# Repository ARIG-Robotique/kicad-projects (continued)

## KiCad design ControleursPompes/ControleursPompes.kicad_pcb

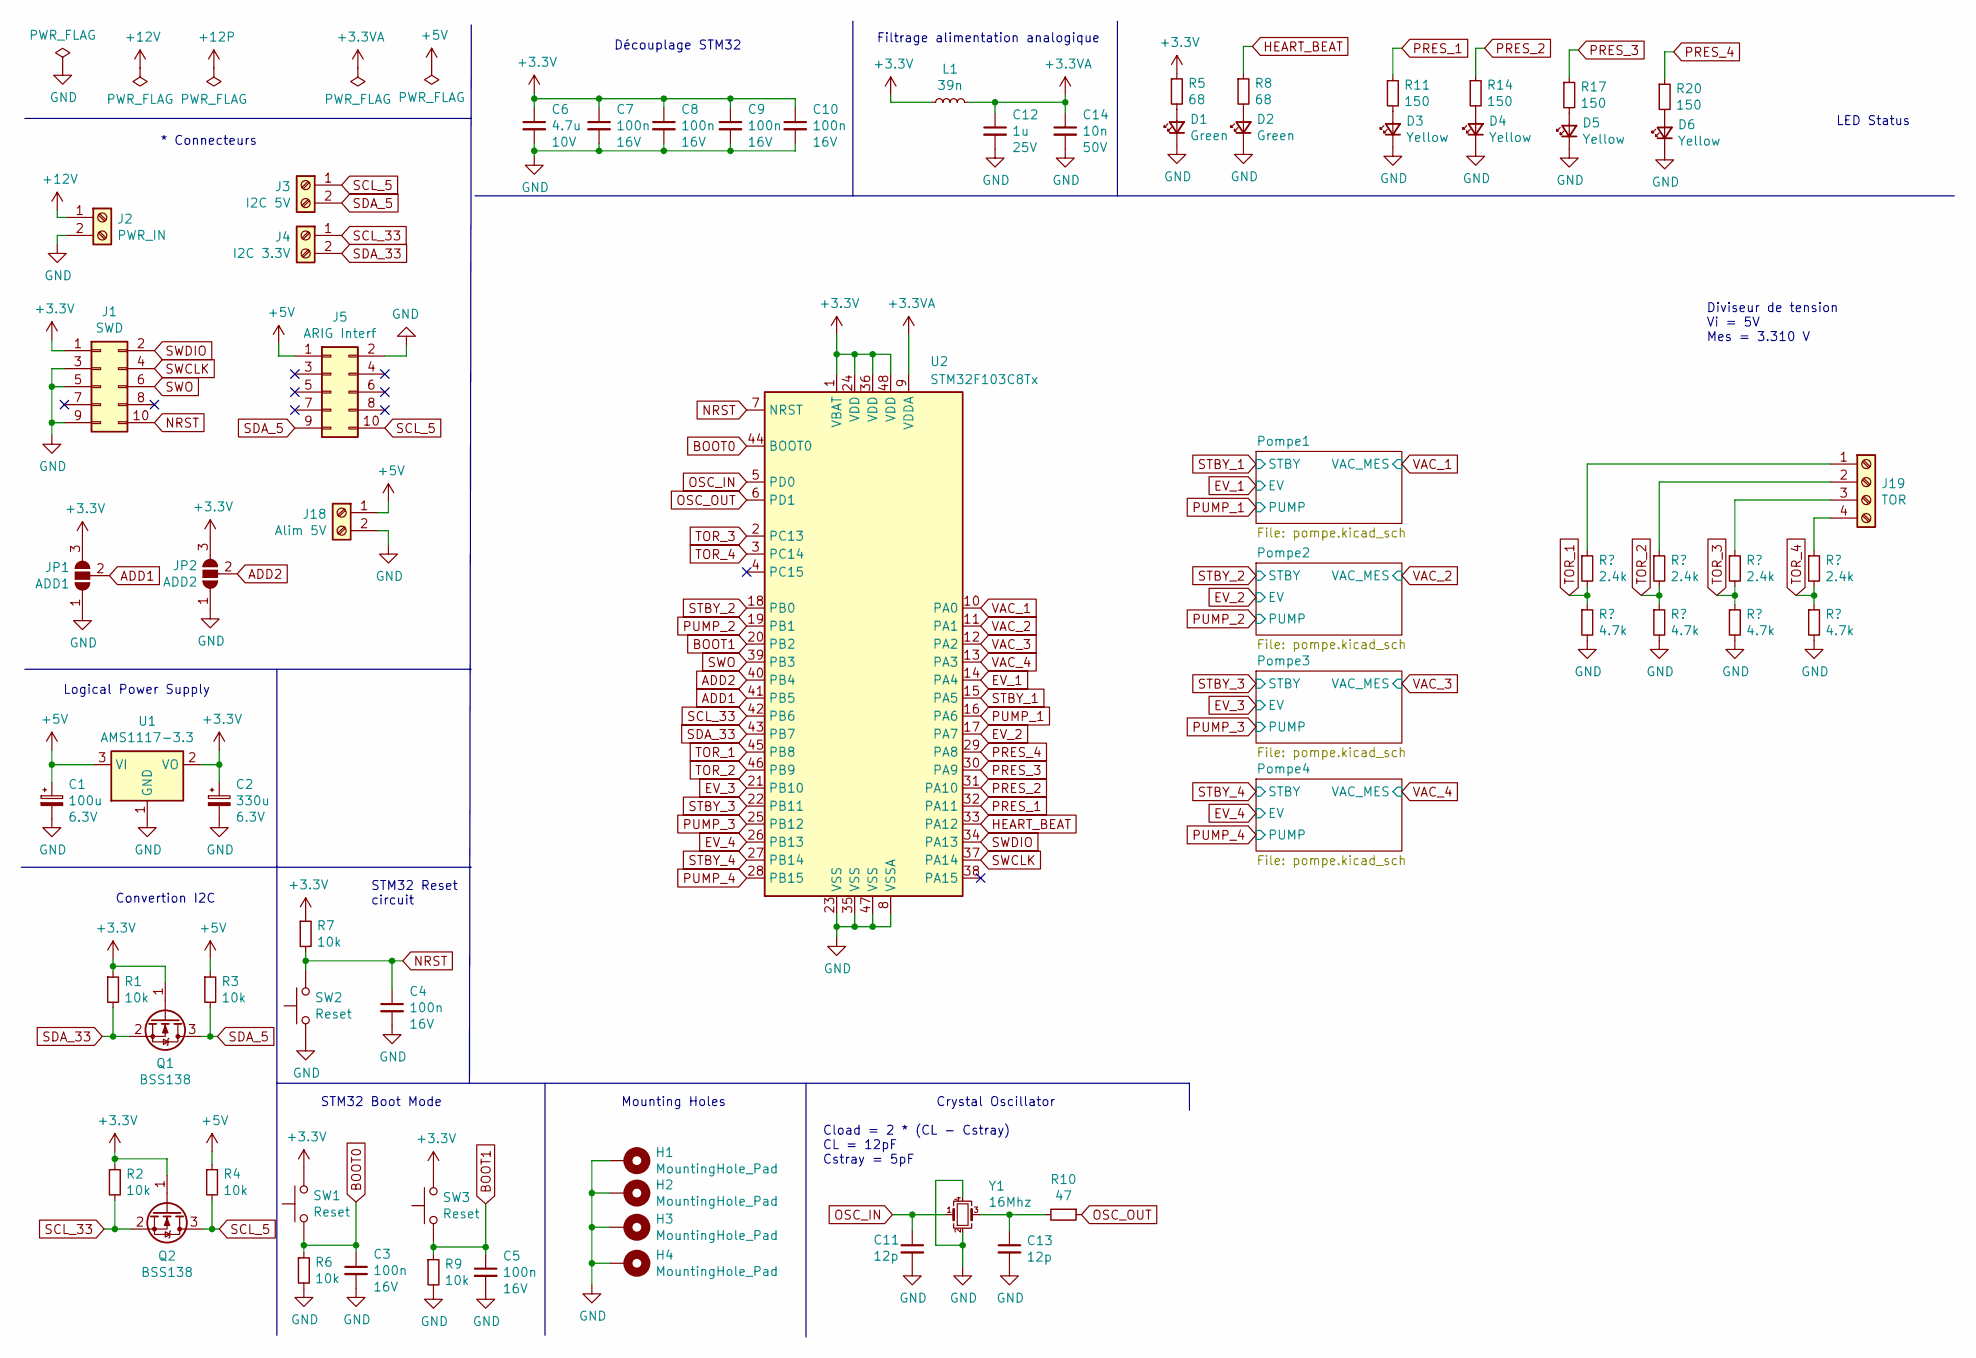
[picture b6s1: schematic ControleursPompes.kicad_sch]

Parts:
C1: 100u; CP_Elec_5x5.3; LCSC Part C249463
C2: 330u; CP_Elec_6.3x7.7; LCSC Part C249900
C3, C4, C5, C7, C8, C9, C10: 100n; C_0402_1005Metric_Pad0.74x0.62mm_HandSolder; LCSC Part C1525
C6: 4.7u; C_0402_1005Metric_Pad0.74x0.62mm_HandSolder; LCSC Part C23733
C11, C13: 12p; C_0402_1005Metric_Pad0.74x0.62mm_HandSolder; LCSC Part C1547
C12: 1u; C_0402_1005Metric_Pad0.74x0.62mm_HandSolder; LCSC Part C52923
C14: 10n; C_0402_1005Metric_Pad0.74x0.62mm_HandSolder; LCSC Part C15195
D1, D2: Green; LED_0805_2012Metric_Pad1.15x1.40mm_HandSolder; LCSC Part C63855
D3, D4, D5, D6: Yellow; LED_0805_2012Metric_Pad1.15x1.40mm_HandSolder; LCSC Part C74346
H1, H2, H3, H4: MountingHole_Pad; MountingHole_3.2mm_M3_Pad_Via; JLCPCB BOM 0
J1: SWD; PinHeader_2x05_P1.27mm_Vertical; JLCPCB BOM 0
J2: PWR_IN; TerminalBlock_Phoenix_MKDS-1,5-2-5.08_1x02_P5.08mm_Horizont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; JLCPCB BOM 0
J3: I2C 5V; TerminalBlock_Phoenix_MPT-0,5-2-2.54_1x02_P2.54mm_Horizontal; JLCPCB BOM 0
J4: I2C 3.3V; TerminalBlock_Phoenix_MPT-0,5-2-2.54_1x02_P2.54mm_Horizontal; JLCPCB BOM 0
J5: ARIG Interf; IDC-Header_2x05_P2.54mm_Vertical; JLCPCB BOM 0
J18: Alim 5V; TerminalBlock_Phoenix_MPT-0,5-2-2.54_1x02_P2.54mm_Horizontal; JLCPCB BOM 0
J19: TOR; TerminalBlock_Phoenix_MPT-0,5-4-2.54_1x04_P2.54mm_Horizontal; JLCPCB BOM 0
JP1: ADD1; SolderJumper-3_P1.3mm_Open_RoundedPad1.0x1.5mm; JLCPCB BOM 0
JP2: ADD2; SolderJumper-3_P1.3mm_Open_RoundedPad1.0x1.5mm; JLCPCB BOM 0
L1: 39n; L_0402_1005Metric_Pad0.77x0.64mm_HandSolder; LCSC Part C26443
Q1, Q2: BSS138; SOT-23; LCSC Part C426569
R1, R2, R3, R4, R6, R7, R9: 10k; R_0805_2012Metric_Pad1.20x1.40mm_HandSolder; LCSC Part C17414
R5, R8: 68; R_0805_2012Metric_Pad1.20x1.40mm_HandSolder; LCSC Part C17802
R10: 47; R_0402_1005Metric_Pad0.72x0.64mm_HandSolder; LCSC Part C25118
R11, R14, R17, R20: 150; R_0805_2012Metric_Pad1.20x1.40mm_HandSolder; LCSC Part C17471
R23, R25, R27, R29: 2.4k; R_0805_2012Metric_Pad1.20x1.40mm_HandSolder; LCSC Part C17526
R24, R26, R28, R30: 4.7k; R_0805_2012Metric_Pad1.20x1.40mm_HandSolder; LCSC Part C17673
SW1, SW2, SW3: Reset; SW_TS_1088_AR_3x4x2; LCSC Part C720477
U1: AMS1117-3.3; SOT-223-3_TabPin2; LCSC Part C6186
U2: STM32F103C8Tx; LQFP-48_7x7mm_P0.5mm; LCSC Part C8734
Y1: 16Mhz; Crystal_SMD_3225-4Pin_3.2x2.5mm_HandSoldering; LCSC Part C13738

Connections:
+3.3VA: C12.1, C14.1, L1.2, U2.9 (VDDA)
+3V3: C2.1, C6.1, C7.1, C8.1, C9.1, C10.1, J1.1, JP1.3 (B), JP2.3 (B), L1.1, Q1.1 (G), Q2.1 (G), R1.1, R2.1, R5.1, R7.1, SW1.1, SW3.1, U1.2 (VO), U2.1 (VBAT), U2.24 (VDD), U2.36 (VDD), U2.48 (VDD); also elsewhere on the board
+5V: C1.1, J5.1, J18.1, R3.1, R4.1, U1.3 (VI)
+12V: J2.1; also elsewhere on the board
ADD1: JP1.2 (C), U2.41 (PB5)
ADD2: JP2.2 (C), U2.40 (PB4)
BOOT0: C3.1, R6.1, SW1.2, U2.44 (BOOT0)
BOOT1: C5.1, R9.1, SW3.2, U2.20 (PB2)
EV_1: U2.14 (PA4); also elsewhere on the board
EV_2: U2.17 (PA7); also elsewhere on the board
EV_3: U2.21 (PB10); also elsewhere on the board
EV_4: U2.26 (PB13); also elsewhere on the board
GND: C1.2, C2.2, C3.2, C4.2, C5.2, C6.2, C7.2, C8.2, C9.2, C10.2, C11.2, C12.2, C13.2, C14.2, D1.1 (K), D2.1 (K), D3.1 (K), D4.1 (K), D5.1 (K), D6.1 (K), H1.1, H2.1, H3.1, H4.1, J1.3, J1.5, J1.9, J2.2, J5.2, J18.2, JP1.1 (A), JP2.1 (A), R6.2, R9.2, R24.2, R26.2, R28.2, R30.2, SW2.2, U1.1 (GND), U2.8 (VSSA), U2.23 (VSS), U2.35 (VSS), U2.47 (VSS), Y1.2, Y1.4; also elsewhere on the board
HEART_BEAT: R8.1, U2.33 (PA12)
NRST: C4.1, J1.10, R7.2, SW2.1, U2.7 (NRST)
unnamed: C13.1, R10.2, Y1.3
unnamed: D1.2 (A), R5.2
unnamed: D2.2 (A), R8.2
unnamed: D3.2 (A), R11.2
unnamed: D4.2 (A), R14.2
unnamed: D5.2 (A), R17.2
unnamed: D6.2 (A), R20.2
unnamed: J19.1, R23.1
unnamed: J19.2, R25.1
unnamed: J19.3, R27.1
unnamed: J19.4, R29.1
OSC_IN: C11.1, U2.5 (PD0), Y1.1
OSC_OUT: R10.1, U2.6 (PD1)
PRES_1: R11.1, U2.32 (PA11)
PRES_2: R14.1, U2.31 (PA10)
PRES_3: R17.1, U2.30 (PA9)
PRES_4: R20.1, U2.29 (PA8)
PUMP_1: U2.16 (PA6); also elsewhere on the board
PUMP_2: U2.19 (PB1); also elsewhere on the board
PUMP_3: U2.25 (PB12); also elsewhere on the board
PUMP_4: U2.28 (PB15); also elsewhere on the board
SCL_5: J3.1, J5.10, Q2.3 (D), R4.2
SCL_33: J4.1, Q2.2 (S), R2.2, U2.42 (PB6)
SDA_5: J3.2, J5.9, Q1.3 (D), R3.2
SDA_33: J4.2, Q1.2 (S), R1.2, U2.43 (PB7)
STBY_1: U2.15 (PA5); also elsewhere on the board
STBY_2: U2.18 (PB0); also elsewhere on the board
STBY_3: U2.22 (PB11); also elsewhere on the board
STBY_4: U2.27 (PB14); also elsewhere on the board
SWCLK: J1.4, U2.37 (PA14)
SWDIO: J1.2, U2.34 (PA13)
SWO: J1.6, U2.39 (PB3)
TOR_1: R23.2, R24.1, U2.45 (PB8)
TOR_2: R25.2, R26.1, U2.46 (PB9)
TOR_3: R27.2, R28.1, U2.2 (PC13)
TOR_4: R29.2, R30.1, U2.3 (PC14)
VAC_1: U2.10 (PA0); also elsewhere on the board
VAC_2: U2.11 (PA1); also elsewhere on the board
VAC_3: U2.12 (PA2); also elsewhere on the board
VAC_4: U2.13 (PA3); also elsewhere on the board

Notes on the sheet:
STM32 Reset circuit
Diviseur de tension Vi = 5V Mes = 3.310 V
Convertion I2C
Logical Power Supply
Mounting Holes
LED Status
Cload = 2 * (CL - Cstray) CL = 12pF Cstray = 5pF
STM32 Boot Mode
Filtrage alimentation analogique
* Connecteurs
Découplage STM32
Crystal Oscillator

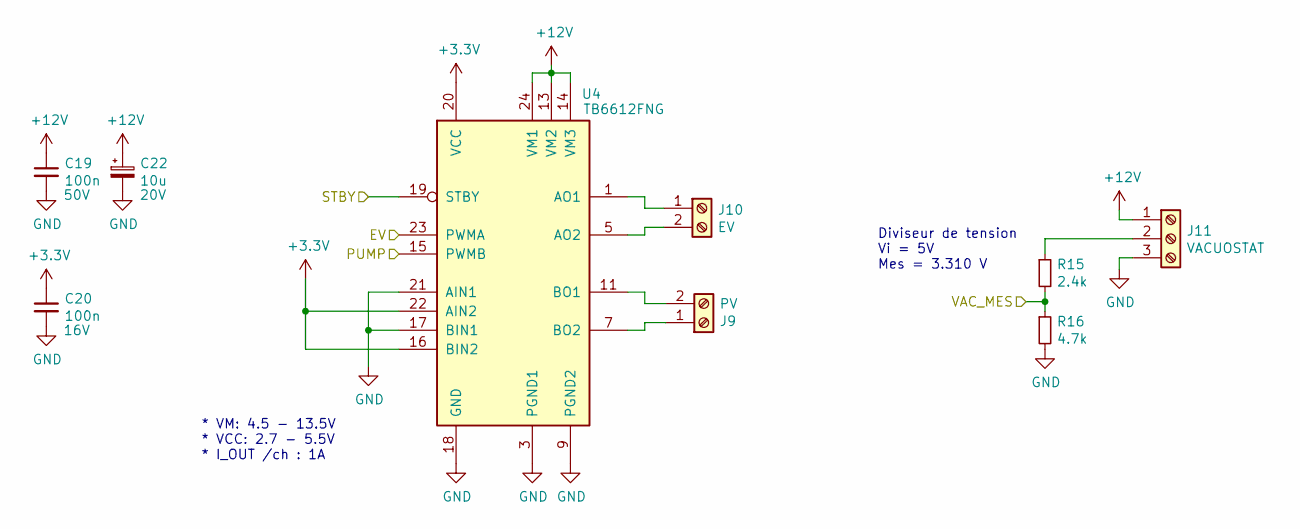
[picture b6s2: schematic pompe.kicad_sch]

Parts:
C19: 100n; C_0805_2012Metric_Pad1.18x1.45mm_HandSolder; LCSC Part C49678
C20: 100n; C_0402_1005Metric_Pad0.74x0.62mm_HandSolder; LCSC Part C1525
C22: 10u; CP_EIA-3528-21_Kemet-B_Pad1.50x2.35mm_HandSolder; LCSC Part C180482
J9: PV; TerminalBlock_Phoenix_MPT-0,5-2-2.54_1x02_P2.54mm_Horizontal; JLCPCB BOM 0
J10: EV; TerminalBlock_Phoenix_MPT-0,5-2-2.54_1x02_P2.54mm_Horizontal; JLCPCB BOM 0
J11: VACUOSTAT; TerminalBlock_Phoenix_MPT-0,5-3-2.54_1x03_P2.54mm_Horizontal; JLCPCB BOM 0
R15: 2.4k; R_0805_2012Metric_Pad1.20x1.40mm_HandSolder; LCSC Part C17526
R16: 4.7k; R_0805_2012Metric_Pad1.20x1.40mm_HandSolder; LCSC Part C17673
U4: TB6612FNG; SSOP-24_5.3x8.2mm_P0.65mm; LCSC Part C88224

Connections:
+3V3: C20.1, U4.16 (BIN2), U4.20 (VCC), U4.22 (AIN2); also elsewhere on the board
+12V: C19.1, C22.1, J11.1, U4.13 (VM2), U4.14 (VM3), U4.24 (VM1); also elsewhere on the board
EV_2: U4.23 (PWMA); also elsewhere on the board
GND: C19.2, C20.2, C22.2, J11.3, R16.2, U4.3 (PGND1), U4.4 (PGND1), U4.9 (PGND2), U4.10 (PGND2), U4.17 (BIN1), U4.18 (GND), U4.21 (AIN1); also elsewhere on the board
unnamed: J9.1, U4.7 (BO2), U4.8 (BO2)
unnamed: J9.2, U4.11 (BO1), U4.12 (BO1)
unnamed: J10.1, U4.1 (AO1), U4.2 (AO1)
unnamed: J10.2, U4.5 (AO2), U4.6 (AO2)
unnamed: J11.2, R15.1
PUMP_2: U4.15 (PWMB); also elsewhere on the board
STBY_2: U4.19 (STBY); also elsewhere on the board
VAC_2: R15.2, R16.1; also elsewhere on the board

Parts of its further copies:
C15, C23, C27: 100n; C_0805_2012Metric_Pad1.18x1.45mm_HandSolder; LCSC Part C49678
C16, C24, C28: 100n; C_0402_1005Metric_Pad0.74x0.62mm_HandSolder; LCSC Part C1525
C18, C26, C30: 10u; CP_EIA-3528-21_Kemet-B_Pad1.50x2.35mm_HandSolder; LCSC Part C180482
J6, J12, J15: PV; TerminalBlock_Phoenix_MPT-0,5-2-2.54_1x02_P2.54mm_Horizontal; JLCPCB BOM 0
J7, J13, J16: EV; TerminalBlock_Phoenix_MPT-0,5-2-2.54_1x02_P2.54mm_Horizontal; JLCPCB BOM 0
J8, J14, J17: VACUOSTAT; TerminalBlock_Phoenix_MPT-0,5-3-2.54_1x03_P2.54mm_Horizontal; JLCPCB BOM 0
R12, R18, R21: 2.4k; R_0805_2012Metric_Pad1.20x1.40mm_HandSolder; LCSC Part C17526
R13, R19, R22: 4.7k; R_0805_2012Metric_Pad1.20x1.40mm_HandSolder; LCSC Part C17673
U3, U5, U6: TB6612FNG; SSOP-24_5.3x8.2mm_P0.65mm; LCSC Part C88224

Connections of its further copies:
+3V3: C16.1, C24.1, C28.1, U3.16 (BIN2), U3.20 (VCC), U3.22 (AIN2), U5.16 (BIN2), U5.20 (VCC), U5.22 (AIN2), U6.16 (BIN2), U6.20 (VCC), U6.22 (AIN2); also elsewhere on the board
+12V: C15.1, C18.1, C23.1, C26.1, C27.1, C30.1, J8.1, J14.1, J17.1, U3.13 (VM2), U3.14 (VM3), U3.24 (VM1), U5.13 (VM2), U5.14 (VM3), U5.24 (VM1), U6.13 (VM2), U6.14 (VM3), U6.24 (VM1); also elsewhere on the board
EV_1: U3.23 (PWMA); also elsewhere on the board
EV_3: U5.23 (PWMA); also elsewhere on the board
EV_4: U6.23 (PWMA); also elsewhere on the board
GND: C15.2, C16.2, C18.2, C23.2, C24.2, C26.2, C27.2, C28.2, C30.2, J8.3, J14.3, J17.3, R13.2, R19.2, R22.2, U3.3 (PGND1), U3.4 (PGND1), U3.9 (PGND2), U3.10 (PGND2), U3.17 (BIN1), U3.18 (GND), U3.21 (AIN1), U5.3 (PGND1), U5.4 (PGND1), U5.9 (PGND2), U5.10 (PGND2), U5.17 (BIN1), U5.18 (GND), U5.21 (AIN1), U6.3 (PGND1), U6.4 (PGND1), U6.9 (PGND2), U6.10 (PGND2), U6.17 (BIN1), U6.18 (GND), U6.21 (AIN1); also elsewhere on the board
unnamed: J6.1, U3.7 (BO2), U3.8 (BO2)
unnamed: J6.2, U3.11 (BO1), U3.12 (BO1)
unnamed: J7.1, U3.1 (AO1), U3.2 (AO1)
unnamed: J7.2, U3.5 (AO2), U3.6 (AO2)
unnamed: J8.2, R12.1
unnamed: J12.1, U5.7 (BO2), U5.8 (BO2)
unnamed: J12.2, U5.11 (BO1), U5.12 (BO1)
unnamed: J13.1, U5.1 (AO1), U5.2 (AO1)
unnamed: J13.2, U5.5 (AO2), U5.6 (AO2)
unnamed: J14.2, R18.1
unnamed: J15.1, U6.7 (BO2), U6.8 (BO2)
unnamed: J15.2, U6.11 (BO1), U6.12 (BO1)
unnamed: J16.1, U6.1 (AO1), U6.2 (AO1)
unnamed: J16.2, U6.5 (AO2), U6.6 (AO2)
unnamed: J17.2, R21.1
PUMP_1: U3.15 (PWMB); also elsewhere on the board
PUMP_3: U5.15 (PWMB); also elsewhere on the board
PUMP_4: U6.15 (PWMB); also elsewhere on the board
STBY_1: U3.19 (STBY); also elsewhere on the board
STBY_3: U5.19 (STBY); also elsewhere on the board
STBY_4: U6.19 (STBY); also elsewhere on the board
VAC_1: R12.2, R13.1; also elsewhere on the board
VAC_3: R18.2, R19.1; also elsewhere on the board
VAC_4: R21.2, R22.1; also elsewhere on the board

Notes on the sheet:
* VM: 4.5 - 13.5V * VCC: 2.7 - 5.5V * I_OUT /ch : 1A
Diviseur de tension Vi = 5V Mes = 3.310 V

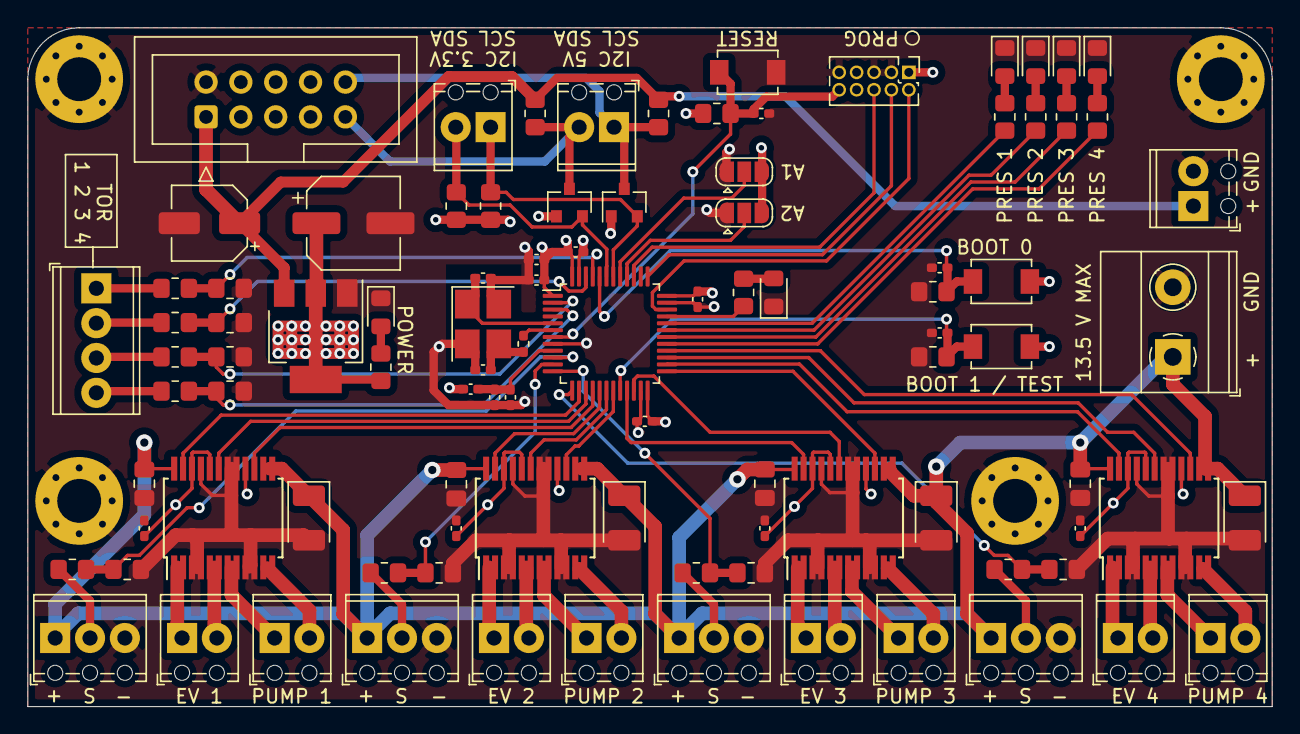
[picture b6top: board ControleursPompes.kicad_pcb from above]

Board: 4 copper layers, 90.8 x 49.5 mm, 100 parts (0 on the bottom side), 75 nets.

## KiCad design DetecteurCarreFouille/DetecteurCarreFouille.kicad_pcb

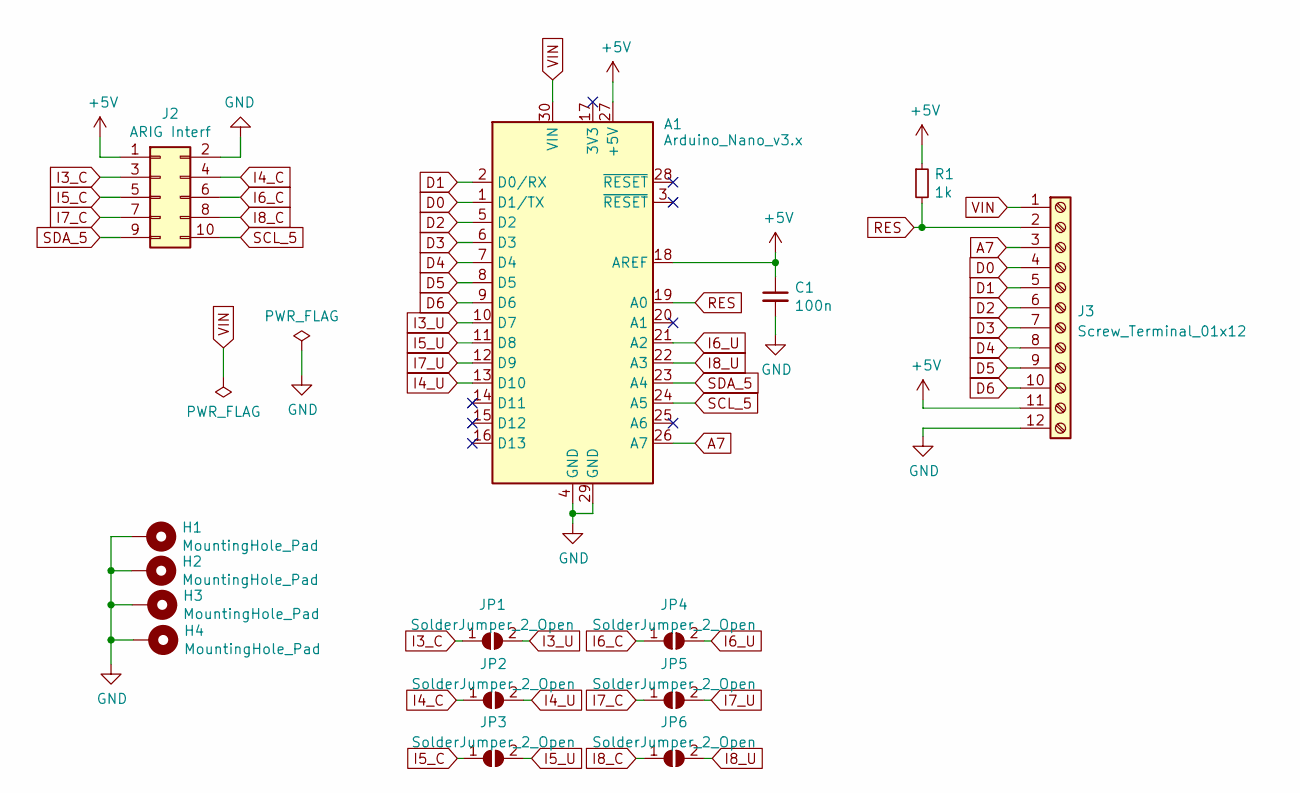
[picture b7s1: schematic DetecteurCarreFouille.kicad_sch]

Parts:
A1: Arduino_Nano_v3.x; Arduino_Nano
C1: 100n; C_Rect_L7.0mm_W2.5mm_P5.00mm
H1, H2, H3, H4: MountingHole_Pad; MountingHole_3.2mm_M3_Pad_Via
J2: ARIG Interf; IDC-Header_2x05_P2.54mm_Vertical
J3: Screw_Terminal_01x12; TerminalBlock_Phoenix_MPT-0,5-12-2.54_1x12_P2.54mm_Horizont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
JP1, JP2, JP3, JP4, JP5, JP6: SolderJumper_2_Open; SolderJumper-2_P1.3mm_Open_RoundedPad1.0x1.5mm
R1: 1k; R_Axial_DIN0309_L9.0mm_D3.2mm_P15.24mm_Horizontal

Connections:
+5V: A1.18 (AREF), A1.27 (+5V), C1.1, J2.1, J3.11, R1.1
A7: A1.26 (A7), J3.3
D0: A1.1 (D1/TX), J3.4
D1: A1.2 (D0/RX), J3.5
D2: A1.5 (D2), J3.6
D3: A1.6 (D3), J3.7
D4: A1.7 (D4), J3.8
D5: A1.8 (D5), J3.9
D6: A1.9 (D6), J3.10
GND: A1.4 (GND), A1.29 (GND), C1.2, H1.1, H2.1, H3.1, H4.1, J2.2, J3.12
I3_C: J2.3, JP1.1 (A)
I3_U: A1.10 (D7), JP1.2 (B)
I4_C: J2.4, JP2.1 (A)
I4_U: A1.13 (D10), JP2.2 (B)
I5_C: J2.5, JP3.1 (A)
I5_U: A1.11 (D8), JP3.2 (B)
I6_C: J2.6, JP4.1 (A)
I6_U: A1.21 (A2), JP4.2 (B)
I7_C: J2.7, JP5.1 (A)
I7_U: A1.12 (D9), JP5.2 (B)
I8_C: J2.8, JP6.1 (A)
I8_U: A1.22 (A3), JP6.2 (B)
RES: A1.19 (A0), J3.2, R1.2
SCL_5: A1.24 (A5), J2.10
SDA_5: A1.23 (A4), J2.9
VIN: A1.30 (VIN), J3.1

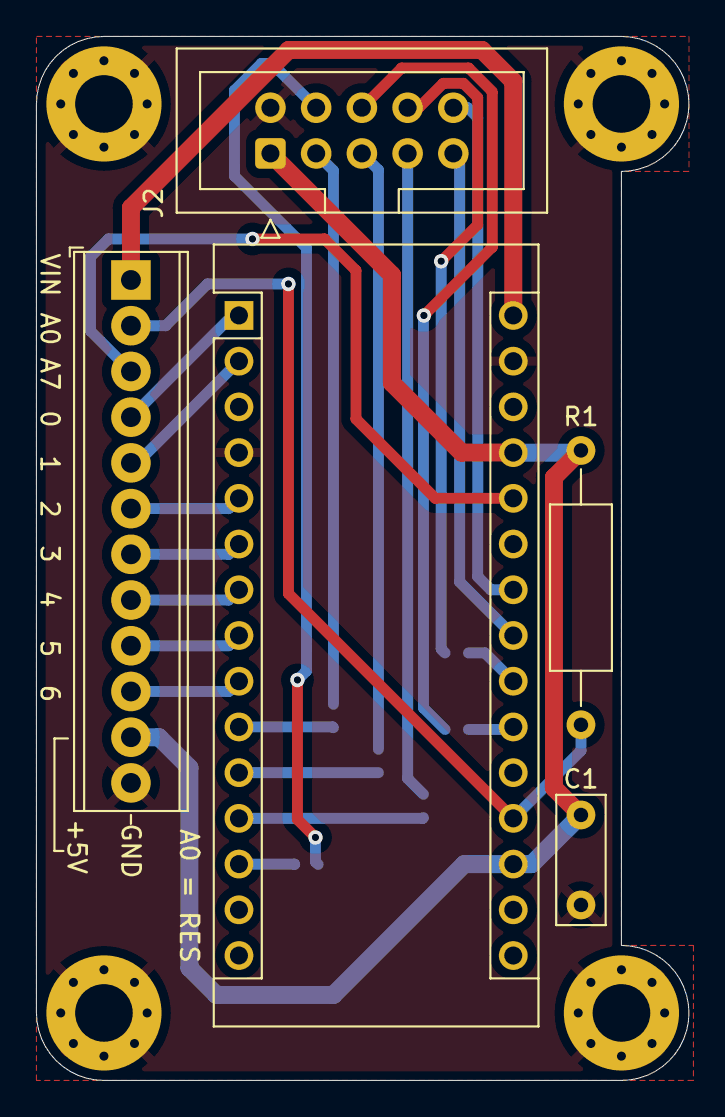
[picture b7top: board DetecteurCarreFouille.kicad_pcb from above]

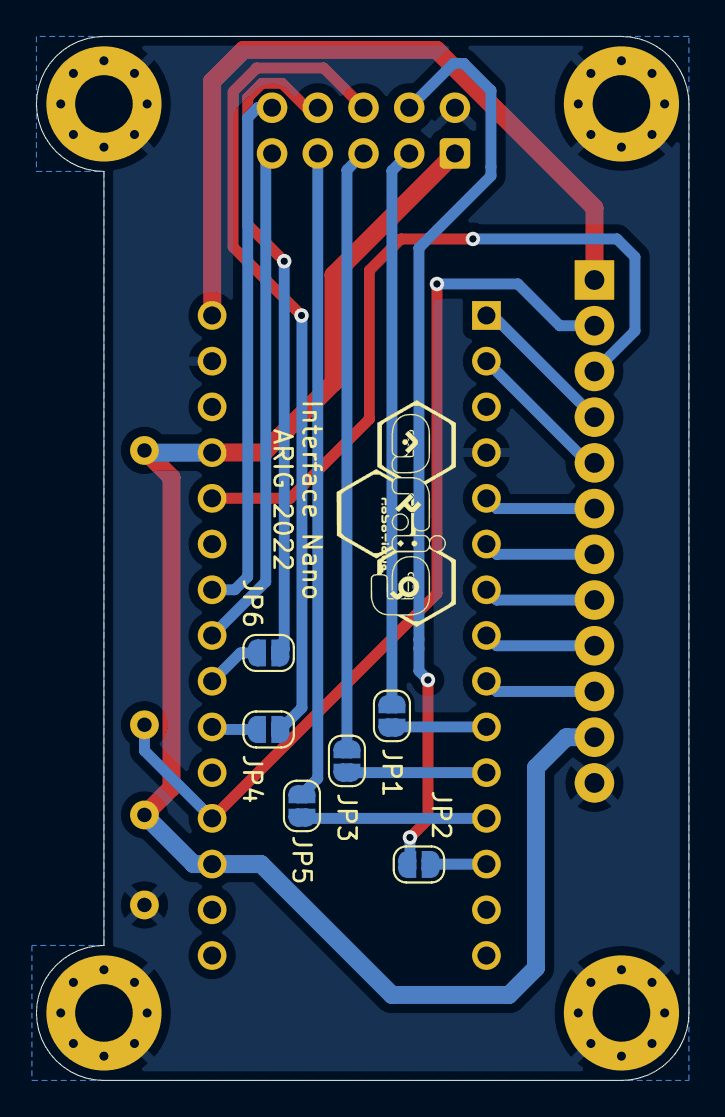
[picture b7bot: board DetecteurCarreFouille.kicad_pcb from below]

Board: 2 copper layers, 36.2 x 58.0 mm, 15 parts (6 on the bottom side), 26 nets.

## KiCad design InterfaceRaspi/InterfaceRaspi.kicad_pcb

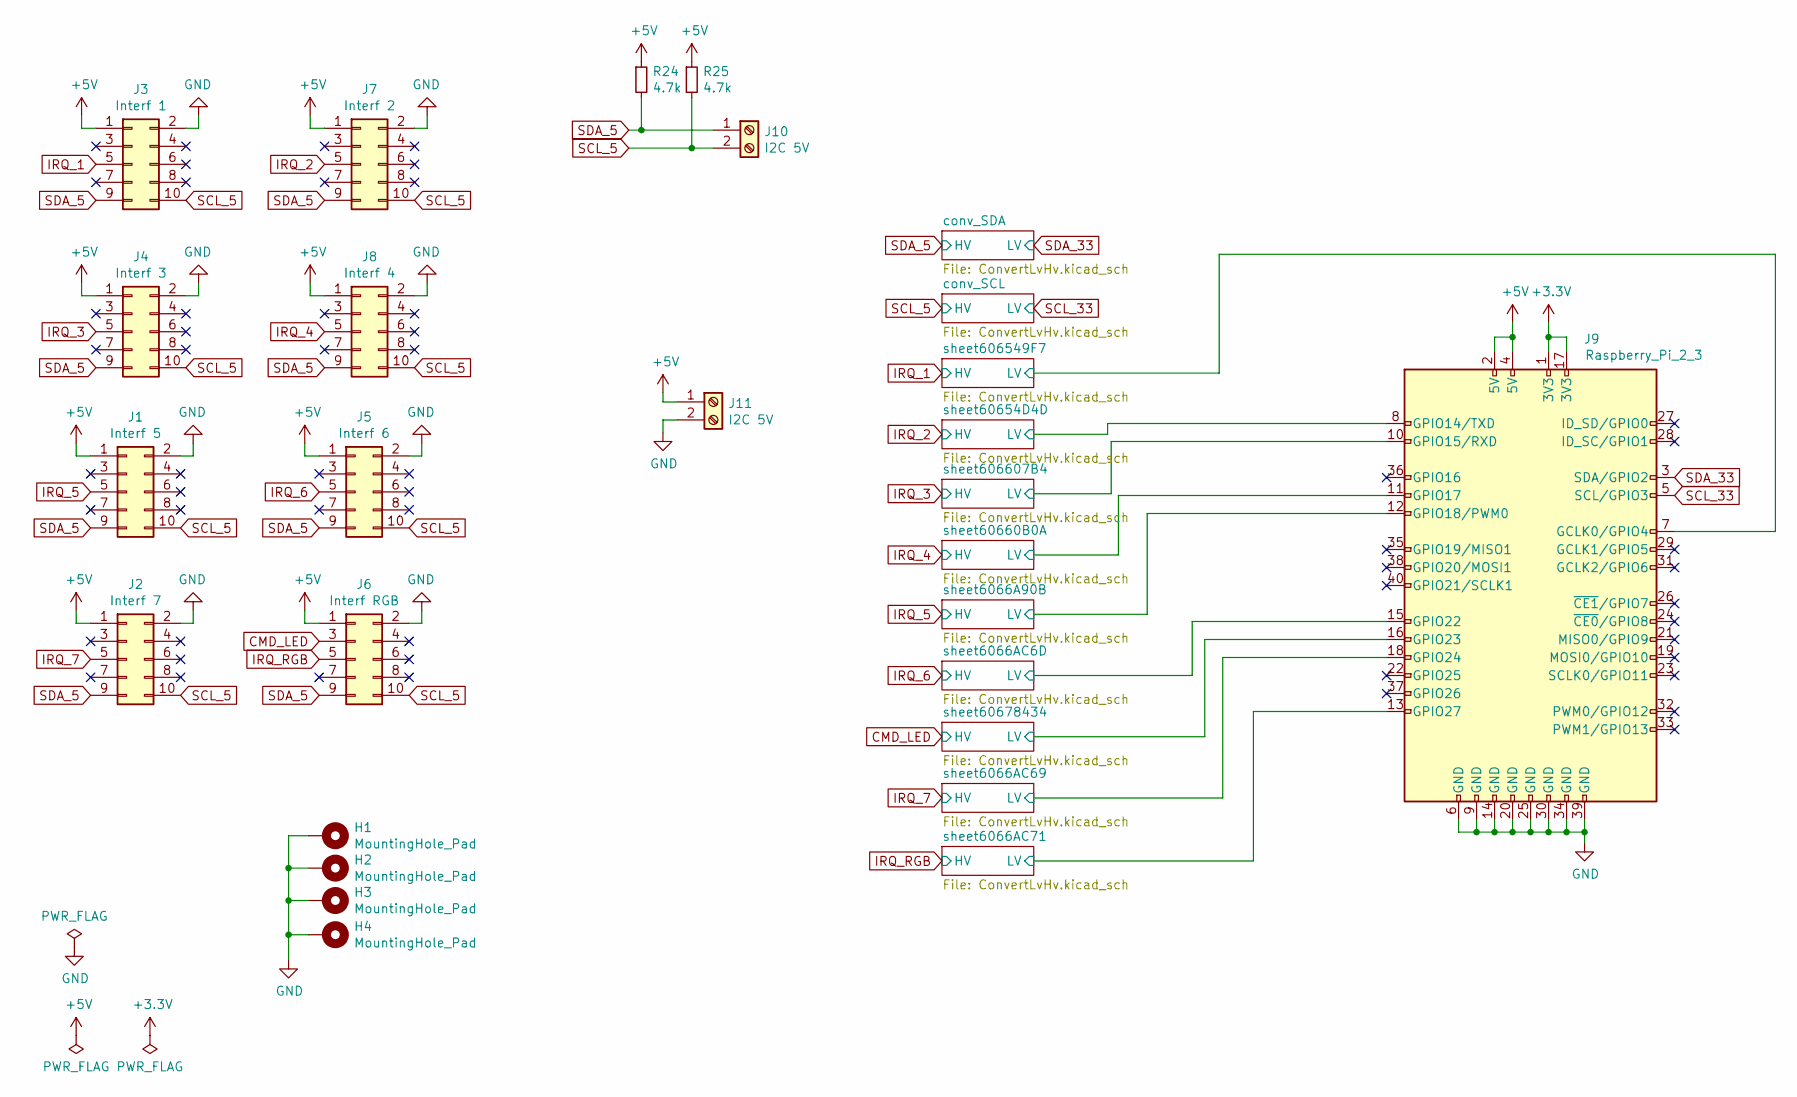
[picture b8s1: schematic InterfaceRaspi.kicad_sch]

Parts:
H1, H2, H3, H4: MountingHole_Pad; MountingHole_3.2mm_M3_ISO14580_Pad; JLCPCB BOM 0
J1: Interf 5; IDC-Header_2x05_P2.54mm_Vertical; JLCPCB BOM 0
J2: Interf 7; IDC-Header_2x05_P2.54mm_Vertical; JLCPCB BOM 0
J3: Interf 1; IDC-Header_2x05_P2.54mm_Vertical; JLCPCB BOM 0
J4: Interf 3; IDC-Header_2x05_P2.54mm_Vertical; JLCPCB BOM 0
J5: Interf 6; IDC-Header_2x05_P2.54mm_Vertical; JLCPCB BOM 0
J6: Interf RGB; IDC-Header_2x05_P2.54mm_Vertical; JLCPCB BOM 0
J7: Interf 2; IDC-Header_2x05_P2.54mm_Vertical; JLCPCB BOM 0
J8: Interf 4; IDC-Header_2x05_P2.54mm_Vertical; JLCPCB BOM 0
J9: Raspberry_Pi_2_3; PinSocket_2x20_P2.54mm_Vertical; JLCPCB BOM 0
J10, J11: I2C 5V; TerminalBlock_Phoenix_MPT-0,5-2-2.54_1x02_P2.54mm_Horizontal; JLCPCB BOM 0
R24, R25: 4.7k; R_0805_2012Metric_Pad1.20x1.40mm_HandSolder; LCSC Part C17673

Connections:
+3V3: J9.1 (3V3), J9.17 (3V3); also elsewhere on the board
+5V: J1.1, J2.1, J3.1, J4.1, J5.1, J6.1, J7.1, J8.1, J9.2 (5V), J9.4 (5V), J11.1, R24.1, R25.1; also elsewhere on the board
/sheet6066A90B/LV: J9.12 (GPIO18/PWM0); also elsewhere on the board
/sheet6066AC6D/LV: J9.15 (GPIO22); also elsewhere on the board
/sheet6066AC69/LV: J9.18 (GPIO24); also elsewhere on the board
/sheet6066AC71/LV: J9.13 (GPIO27); also elsewhere on the board
/sheet60654D4D/LV: J9.8 (GPIO14/TXD); also elsewhere on the board
/sheet60660B0A/LV: J9.11 (GPIO17); also elsewhere on the board
/sheet606549F7/LV: J9.7 (GCLK0/GPIO4); also elsewhere on the board
/sheet606607B4/LV: J9.10 (GPIO15/RXD); also elsewhere on the board
/sheet60678434/LV: J9.16 (GPIO23); also elsewhere on the board
CMD_LED: J6.3; also elsewhere on the board
GND: H1.1, H2.1, H3.1, H4.1, J1.2, J2.2, J3.2, J4.2, J5.2, J6.2, J7.2, J8.2, J9.6 (GND), J9.9 (GND), J9.14 (GND), J9.20 (GND), J9.25 (GND), J9.30 (GND), J9.34 (GND), J9.39 (GND), J11.2
IRQ_1: J3.5; also elsewhere on the board
IRQ_2: J7.5; also elsewhere on the board
IRQ_3: J4.5; also elsewhere on the board
IRQ_4: J8.5; also elsewhere on the board
IRQ_5: J1.5; also elsewhere on the board
IRQ_6: J5.5; also elsewhere on the board
IRQ_7: J2.5; also elsewhere on the board
IRQ_RGB: J6.5; also elsewhere on the board
SCL_5: J1.10, J2.10, J3.10, J4.10, J5.10, J6.10, J7.10, J8.10, J10.2, R25.2; also elsewhere on the board
SCL_33: J9.5 (SCL/GPIO3); also elsewhere on the board
SDA_5: J1.9, J2.9, J3.9, J4.9, J5.9, J6.9, J7.9, J8.9, J10.1, R24.2; also elsewhere on the board
SDA_33: J9.3 (SDA/GPIO2); also elsewhere on the board

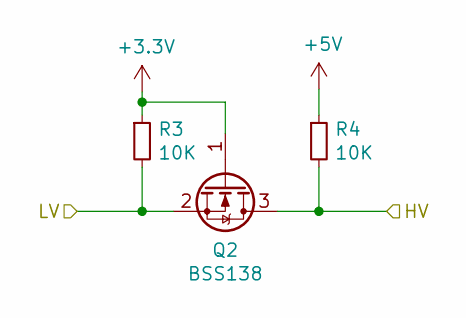
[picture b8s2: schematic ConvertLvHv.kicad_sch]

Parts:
Q2: BSS138; SOT-23; LCSC Part C426569
R3, R4: 10K; R_0805_2012Metric_Pad1.20x1.40mm_HandSolder; LCSC Part C17414

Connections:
+3V3: Q2.1 (G), R3.1; also elsewhere on the board
+5V: R4.1; also elsewhere on the board
SCL_5: Q2.3 (D), R4.2; also elsewhere on the board
SCL_33: Q2.2 (S), R3.2; also elsewhere on the board

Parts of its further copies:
Q1, Q3, Q4, Q5, Q6, Q7, Q8, Q9, Q10, Q11: BSS138; SOT-23; LCSC Part C426569
R1, R2, R5, R6, R7, R8, R9, R10, R11, R12, R13, R14, R15, R16, R17, R18, R19, R20, R21, R22: 10K; R_0805_2012Metric_Pad1.20x1.40mm_HandSolder; LCSC Part C17414

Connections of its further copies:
+3V3: Q1.1 (G), Q3.1 (G), Q4.1 (G), Q5.1 (G), Q6.1 (G), Q7.1 (G), Q8.1 (G), Q9.1 (G), Q10.1 (G), Q11.1 (G), R1.1, R5.1, R7.1, R9.1, R11.1, R13.1, R15.1, R17.1, R19.1, R21.1; also elsewhere on the board
+5V: R2.1, R6.1, R8.1, R10.1, R12.1, R14.1, R16.1, R18.1, R20.1, R22.1; also elsewhere on the board
/sheet6066A90B/LV: Q7.2 (S), R13.2; also elsewhere on the board
/sheet6066AC6D/LV: Q9.2 (S), R17.2; also elsewhere on the board
/sheet6066AC69/LV: Q8.2 (S), R15.2; also elsewhere on the board
/sheet6066AC71/LV: Q10.2 (S), R19.2; also elsewhere on the board
/sheet60654D4D/LV: Q4.2 (S), R7.2; also elsewhere on the board
/sheet60660B0A/LV: Q6.2 (S), R11.2; also elsewhere on the board
/sheet606549F7/LV: Q3.2 (S), R5.2; also elsewhere on the board
/sheet606607B4/LV: Q5.2 (S), R9.2; also elsewhere on the board
/sheet60678434/LV: Q11.2 (S), R21.2; also elsewhere on the board
CMD_LED: Q11.3 (D), R22.2; also elsewhere on the board
IRQ_1: Q3.3 (D), R6.2; also elsewhere on the board
IRQ_2: Q4.3 (D), R8.2; also elsewhere on the board
IRQ_3: Q5.3 (D), R10.2; also elsewhere on the board
IRQ_4: Q6.3 (D), R12.2; also elsewhere on the board
IRQ_5: Q7.3 (D), R14.2; also elsewhere on the board
IRQ_6: Q9.3 (D), R18.2; also elsewhere on the board
IRQ_7: Q8.3 (D), R16.2; also elsewhere on the board
IRQ_RGB: Q10.3 (D), R20.2; also elsewhere on the board
SDA_5: Q1.3 (D), R2.2; also elsewhere on the board
SDA_33: Q1.2 (S), R1.2; also elsewhere on the board

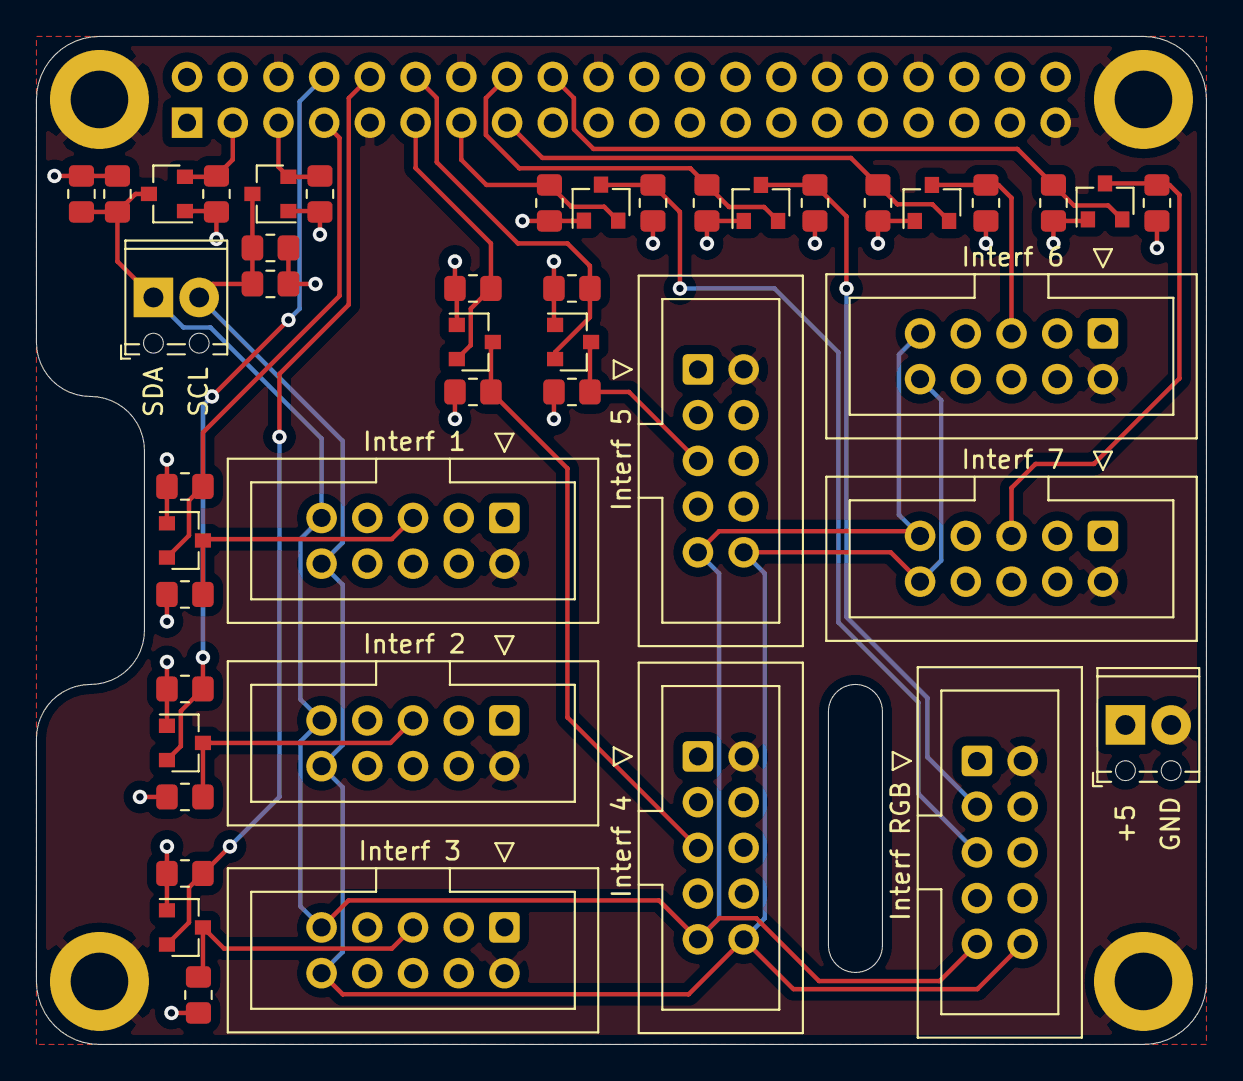
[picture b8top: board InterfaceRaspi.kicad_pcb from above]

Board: 4 copper layers, 65.0 x 56.0 mm, 50 parts (1 on the bottom side), 25 nets.
